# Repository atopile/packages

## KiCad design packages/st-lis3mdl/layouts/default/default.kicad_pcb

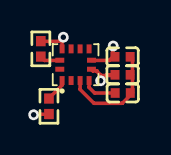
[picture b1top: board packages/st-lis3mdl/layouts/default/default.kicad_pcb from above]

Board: 2 copper layers, 6 parts (0 on the bottom side), 7 nets.

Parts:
C1, C2, C3: 1±10.0%F; C0402
R1, R2: 10000±1.0%Ω; R0402
U1: LGA-12_L2.0-W2.0-P0.50-BL

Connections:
Res: U1.2, U1.12
SCL: R1.1, U1.1
SDA: R2.1, U1.11
decoupling_caps[0]-power-hv: C1.1, U1.5
decoupling_caps[2]-power-hv: C3.1, U1.4
hv: C2.1, R1.2, R2.2, U1.6, U1.10
power-lv: C1.2, C2.2, C3.2, U1.3

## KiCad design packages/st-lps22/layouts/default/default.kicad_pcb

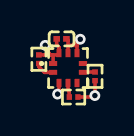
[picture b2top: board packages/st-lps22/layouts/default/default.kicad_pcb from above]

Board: 2 copper layers, 5 parts (0 on the bottom side), 5 nets.

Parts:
C1: 1±10.0%F; C0201
R1, R2, R3: 10000±1.0%Ω; R0201
U1: HLGA-10L_LPS22HBTR

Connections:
CS: R3.2, U1.6
MOSI: R2.1, U1.4
SCL: R1.1, U1.2
hv: C1.1, R1.2, R2.2, R3.1, U1.1, U1.10
lv: C1.2, U1.3, U1.5, U1.8, U1.9

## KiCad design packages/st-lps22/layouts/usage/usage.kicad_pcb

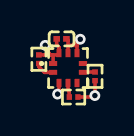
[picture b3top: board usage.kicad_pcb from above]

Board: 2 copper layers, 5 parts (0 on the bottom side), 5 nets.

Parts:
C1: 1±10.0%F; C0201
R1, R2, R3: 10000±1.0%Ω; R0201
U1: HLGA-10L_LPS22HBTR

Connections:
CS: R1.2, U1.6
SCL: R2.1, U1.2
SDA: R3.1, U1.4
hv: C1.1, R1.1, R2.2, R3.2, U1.1, U1.10
lv: C1.2, U1.3, U1.5, U1.8, U1.9

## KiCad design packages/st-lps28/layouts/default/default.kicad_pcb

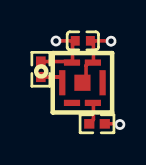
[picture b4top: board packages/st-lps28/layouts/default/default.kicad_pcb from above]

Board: 2 copper layers, 4 parts (0 on the bottom side), 4 nets.

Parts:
C1: 0F; C0402
R1, R2: 10000Ω; R0402
U1: SENSOR-SMD_LPS28DFWTR

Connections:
SCL: R1.1, U1.3
SDA: R2.1, U1.1
hv: C1.1, R1.2, R2.2, U1.6
lv: C1.2, U1.2, U1.5, U1.7

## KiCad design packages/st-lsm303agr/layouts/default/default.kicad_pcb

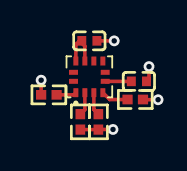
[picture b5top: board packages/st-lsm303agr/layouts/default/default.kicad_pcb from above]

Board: 2 copper layers, 7 parts (0 on the bottom side), 7 nets.

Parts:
C1: 100nF; C0402
C3: 220nF; C0402
R1, R2: 10kΩ; R0402
R3, R4: 4.7kΩ; R0402
U1: LGA-12_L2.0-W2.0-P0.50-BL

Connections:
CS_MAG: R1.2, U1.3
CS_XL: R2.2, U1.2
SCL: R3.1, U1.1
SDA: R4.1, U1.4
hv: C1.1, R1.1, R2.1, R3.2, R4.2, U1.9, U1.10
internal_regulation_capacitor-power-hv: C1.2, C3.1, U1.6, U1.8
lv: C3.2, U1.5
